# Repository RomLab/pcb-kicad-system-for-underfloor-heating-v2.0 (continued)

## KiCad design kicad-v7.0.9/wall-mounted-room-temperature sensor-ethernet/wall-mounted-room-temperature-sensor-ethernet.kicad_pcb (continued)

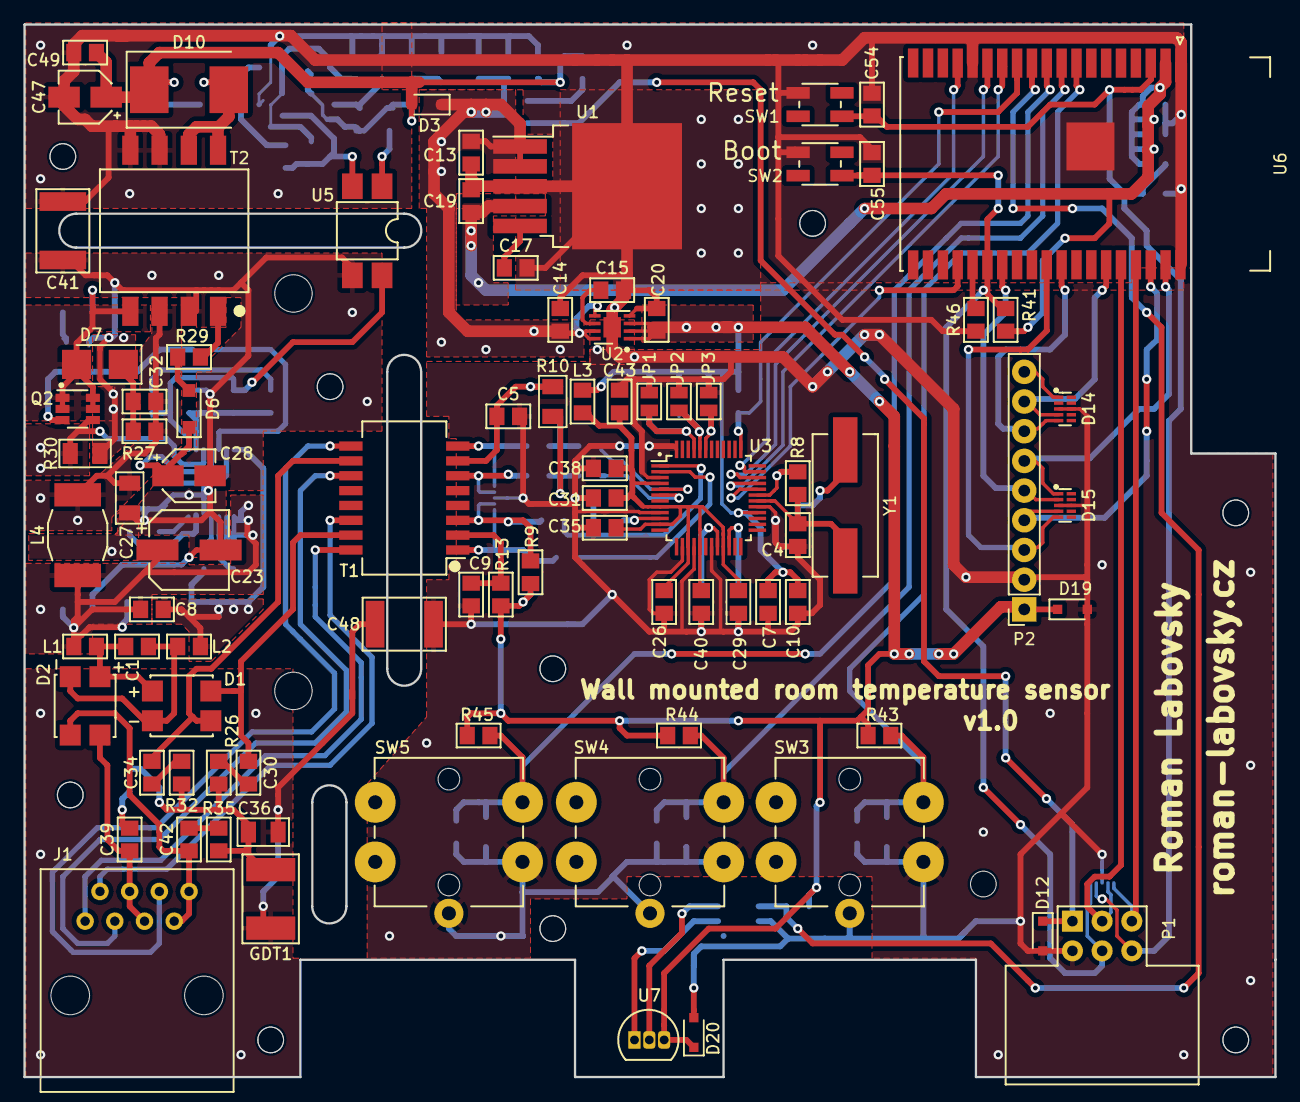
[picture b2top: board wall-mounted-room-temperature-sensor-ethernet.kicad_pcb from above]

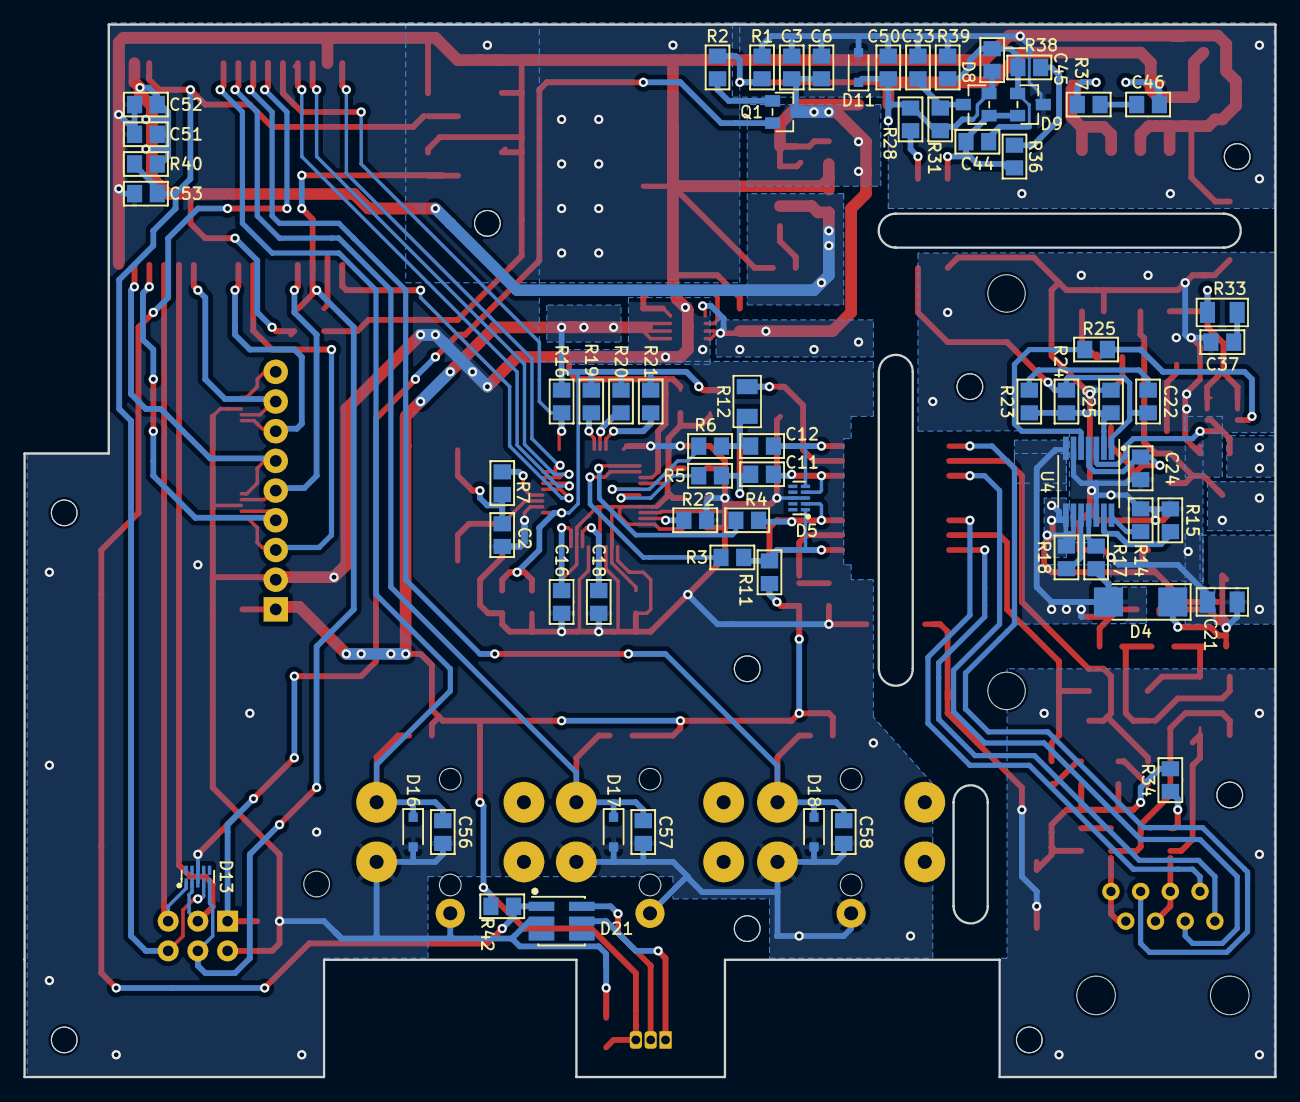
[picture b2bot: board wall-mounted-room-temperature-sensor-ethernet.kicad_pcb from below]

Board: 2 copper layers, 107.0 x 90.0 mm, 165 parts (66 on the bottom side), 97 nets.

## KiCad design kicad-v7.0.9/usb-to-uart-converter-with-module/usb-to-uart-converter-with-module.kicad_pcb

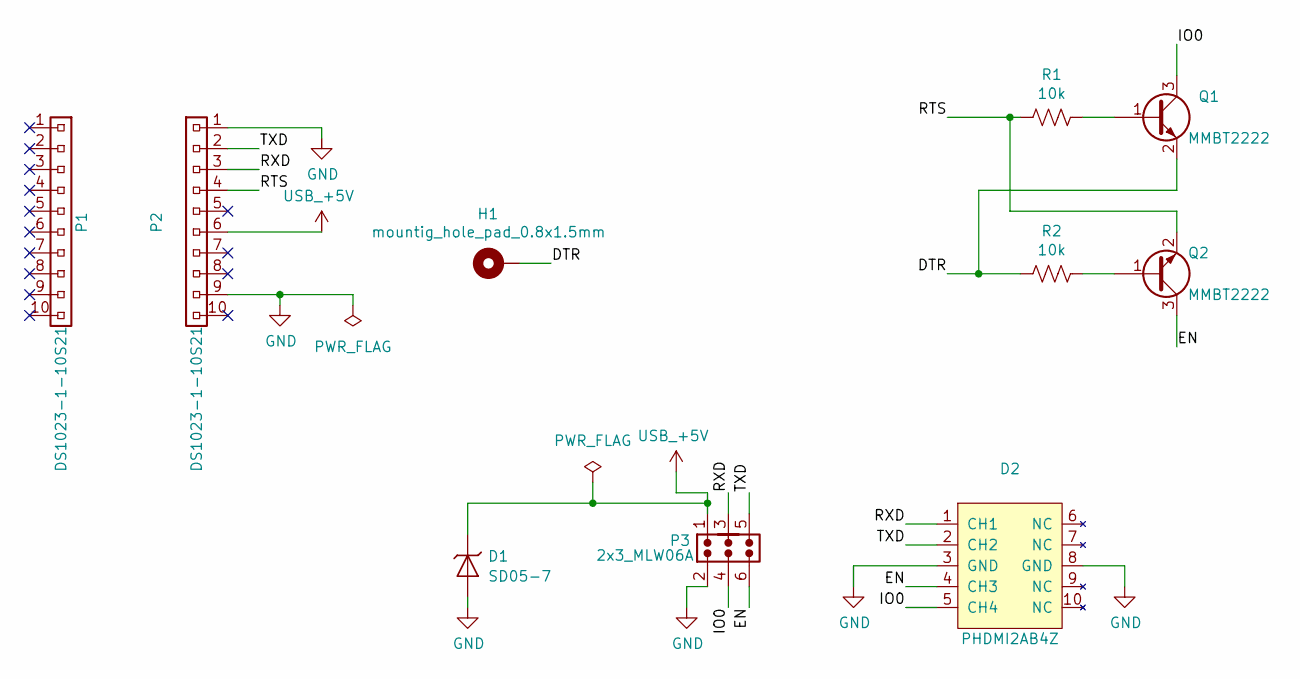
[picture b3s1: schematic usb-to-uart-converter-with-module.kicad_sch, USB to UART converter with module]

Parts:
D1: SD05-7; sod_323
D2: PHDMI2AB4Z; dfn_2510a_10
H1: mountig_hole_pad_0.8x1.5mm
P1, P2: DS1023-1-10S21; 1x10_pin_socket_2.54mm_vertical_8.5mm
P3: 2x3_MLW06A
Q1, Q2: MMBT2222; sot_23_3
R1, R2: 10k; r_0805

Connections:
/DTR: H1.1, Q1.2 (E), R2.1
/EN: D2.4 (CH3), P3.6, Q2.3 (C)
/IO0: D2.5 (CH4), P3.4, Q1.3 (C)
/RTS: P2.4, Q2.2 (E), R1.1
/RXD: D2.1 (CH1), P2.3, P3.3
/TXD: D2.2 (CH2), P2.2, P3.5
GND: D1.2 (A), D2.3 (GND), D2.8 (GND), P2.1, P2.9, P3.2
unnamed: Q1.1 (B), R1.2
unnamed: Q2.1 (B), R2.2
USB_+5V: D1.1 (K), P2.6, P3.1

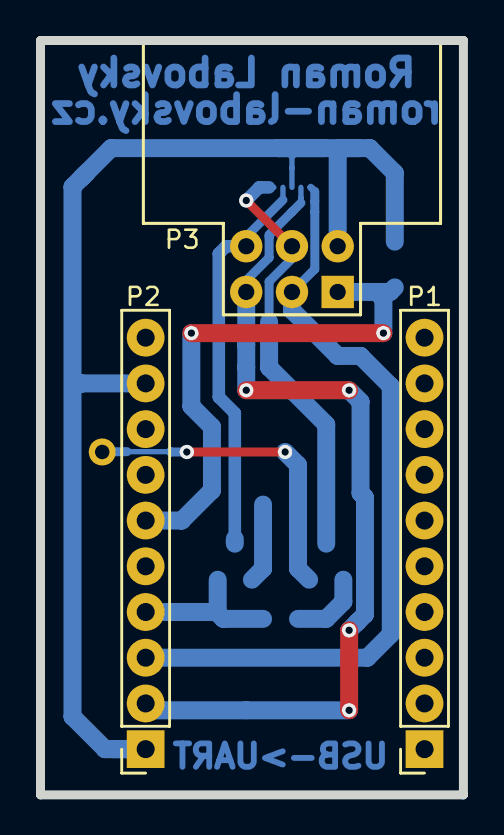
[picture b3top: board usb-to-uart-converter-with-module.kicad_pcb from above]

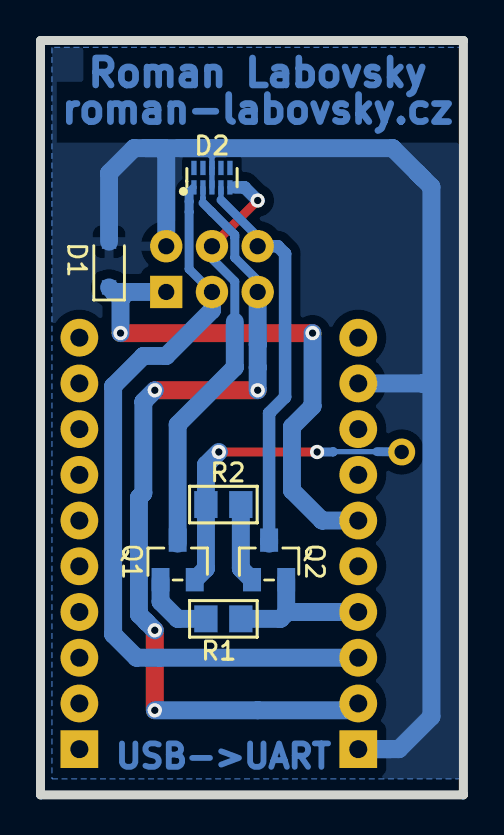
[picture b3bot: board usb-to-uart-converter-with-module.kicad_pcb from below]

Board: 2 copper layers, 23.5 x 41.9 mm, 10 parts (7 on the bottom side), 10 nets.

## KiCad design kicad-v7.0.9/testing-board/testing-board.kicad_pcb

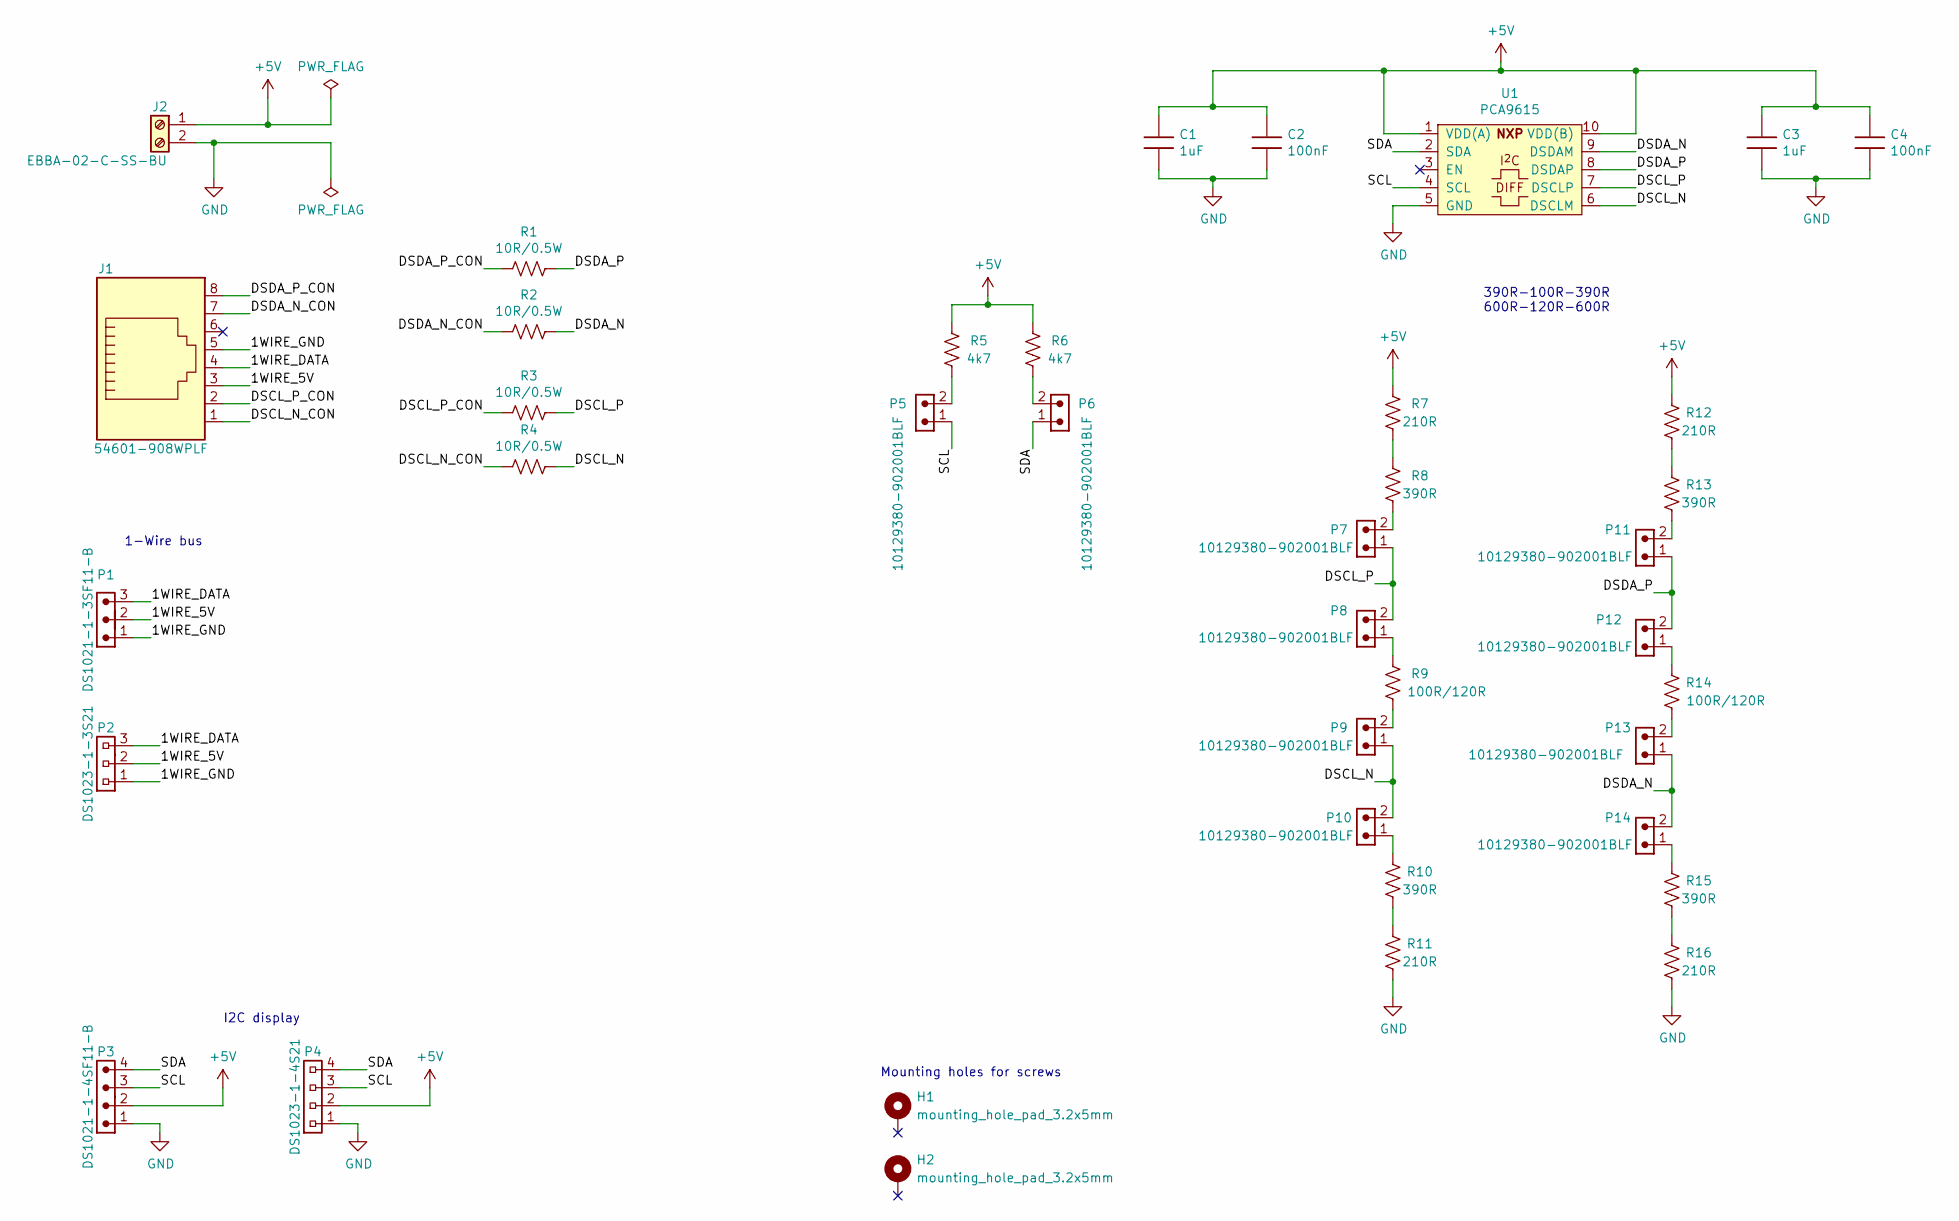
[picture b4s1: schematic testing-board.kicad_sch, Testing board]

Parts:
C1, C3: 1uF; c_1206
C2, C4: 100nF; c_1206
H1, H2: mounting_hole_pad_3.2x5mm
J1: 54601-908WPLF
J2: EBBA-02-C-SS-BU
P1: DS1021-1-3SF11-B; 1x3_pin_header_2.54mm_vertical
P2: DS1023-1-3S21; 1x3_pin_socket_2.54mm_vertical_8.5mm
P3: DS1021-1-4SF11-B; 1x4_pin_header_2.54mm_vertical
P4: DS1023-1-4S21; 1x4_pin_socket_2.54mm_vertical_8.5mm
P5, P6, P7, P8, P9, P10, P11, P12, P13, P14: 10129380-902001BLF; 1x2_pin_header_2.54mm_vertical
R1, R2, R3, R4: 10R/0.5W; r_1206
R5, R6: 4k7; r_1206
R7, R11, R12, R16: 210R; r_1206
R8, R10, R13, R15: 390R; r_1206
R9, R14: 100R/120R; r_1206
U1: PCA9615; tssop_10

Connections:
+5V: C1.1, C2.1, C3.1, C4.1, J2.1, P3.2, P4.2, R5.1, R6.1, R7.1, R12.1, U1.1 (VDD(A)), U1.10 (VDD(B))
/1WIRE_5V: J1.3, P1.2, P2.2
/1WIRE_DATA: J1.4, P1.3, P2.3
/1WIRE_GND: J1.5, P1.1, P2.1
/DSCL_N: P9.1, P10.2, R4.2, U1.6 (DSCLM)
/DSCL_N_CON: J1.1, R4.1
/DSCL_P: P7.1, P8.2, R3.2, U1.7 (DSCLP)
/DSCL_P_CON: J1.2, R3.1
/DSDA_N: P13.1, P14.2, R2.2, U1.9 (DSDAM)
/DSDA_N_CON: J1.7, R2.1
/DSDA_P: P11.1, P12.2, R1.2, U1.8 (DSDAP)
/DSDA_P_CON: J1.8, R1.1
/SCL: P3.3, P4.3, P5.1, U1.4 (SCL)
/SDA: P3.4, P4.4, P6.1, U1.2 (SDA)
GND: C1.2, C2.2, C3.2, C4.2, J2.2, P3.1, P4.1, R11.2, R16.2, U1.5 (GND)
unnamed: P5.2, R5.2
unnamed: P6.2, R6.2
unnamed: P7.2, R8.2
unnamed: P8.1, R9.1
unnamed: P9.2, R9.2
unnamed: P10.1, R10.1
unnamed: P11.2, R13.2
unnamed: P12.1, R14.1
unnamed: P13.2, R14.2
unnamed: P14.1, R15.1
unnamed: R7.2, R8.1
unnamed: R10.2, R11.1
unnamed: R12.2, R13.1
unnamed: R15.2, R16.1

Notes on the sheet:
1-Wire bus
Mounting holes for screws
I2C display
390R-100R-390R 600R-120R-600R

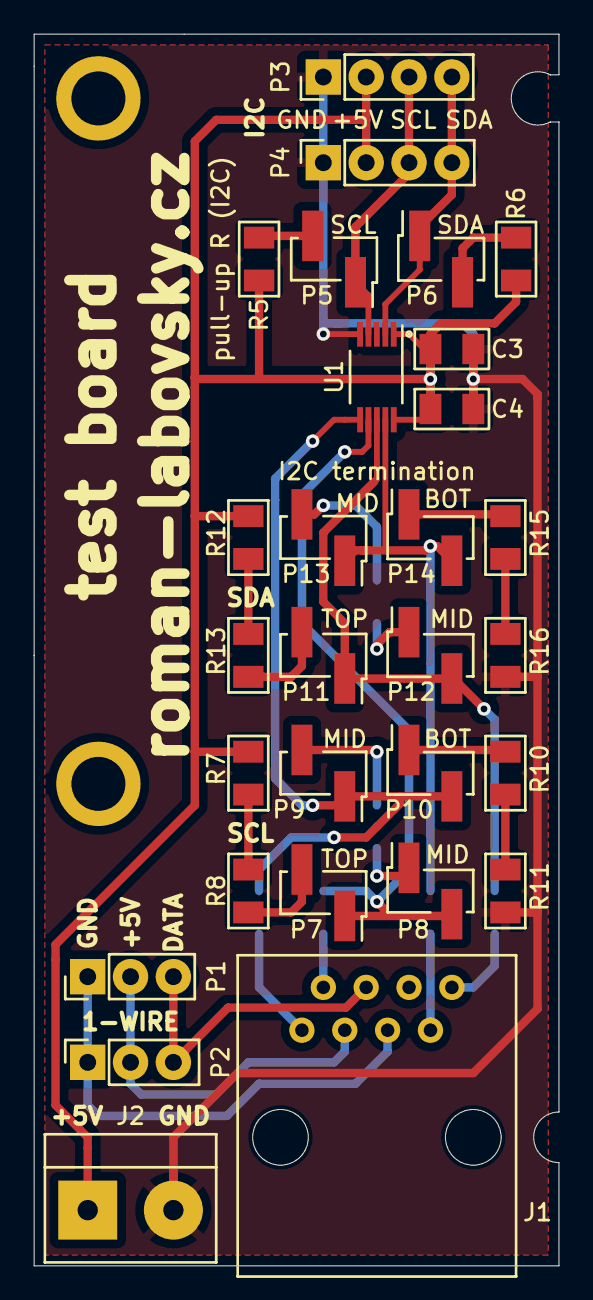
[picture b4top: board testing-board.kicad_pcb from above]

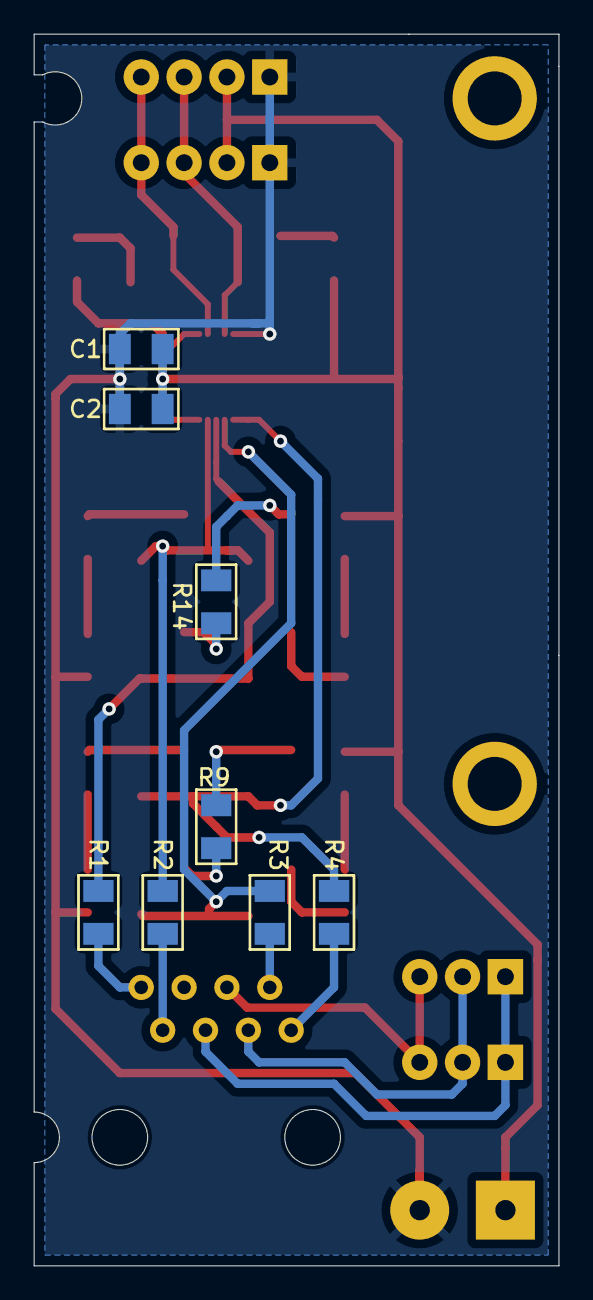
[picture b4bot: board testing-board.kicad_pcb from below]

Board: 2 copper layers, 31.1 x 73.0 mm, 39 parts (8 on the bottom side), 29 nets.

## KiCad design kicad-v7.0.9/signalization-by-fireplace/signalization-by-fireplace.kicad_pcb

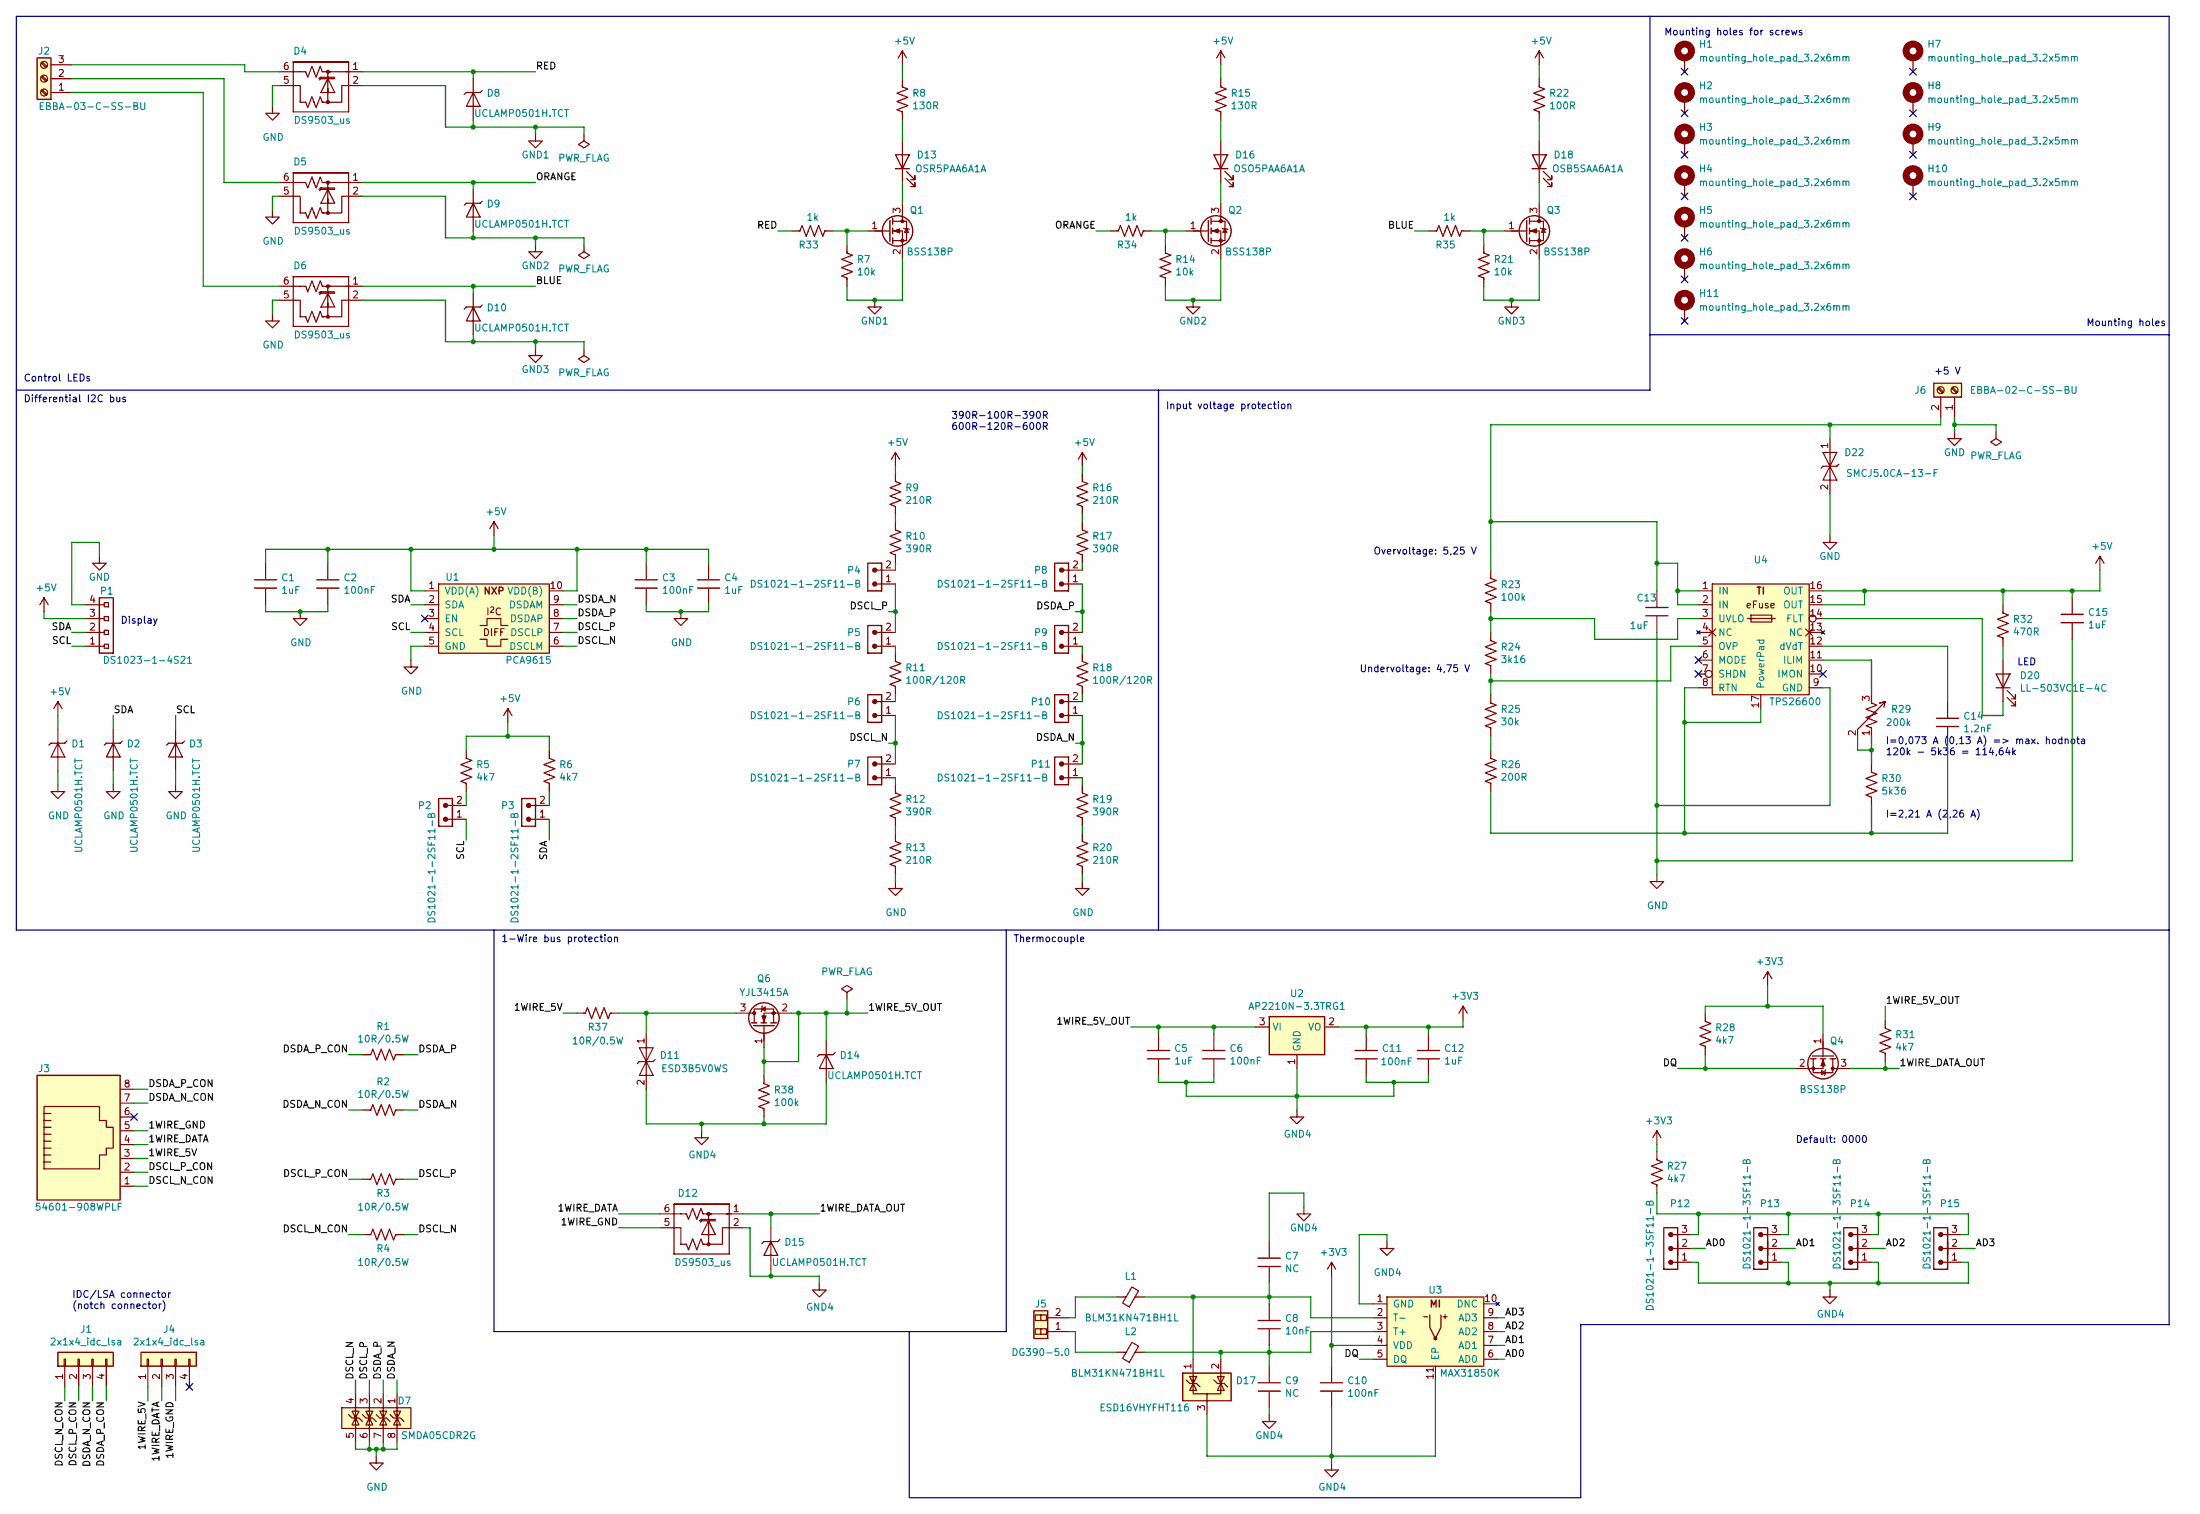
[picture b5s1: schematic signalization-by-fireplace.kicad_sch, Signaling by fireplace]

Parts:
C1, C4, C5, C12, C13, C15: 1uF; c_1206
C2, C3, C6, C10, C11: 100nF; c_1206
C7, C9: NC; c_1206
C8: 10nF; c_1206
C14: 1.2nF; c_1206
D1, D2, D3, D8, D9, D10, D14, D15: UCLAMP0501H.TCT; sod_523
D4, D5, D6, D12: DS9503_us; tsoc_6
D7: SMDA05CDR2G; soic_8_3.9mmx4.9mm
D11: ESD3B5V0WS; sod_323
D13: OSR5PAA6A1A; led_d10mm_2.54mm
D16: OSO5PAA6A1A; led_d10mm_2.54mm
D17: ESD16VHYFHT116; sot_23
D18: OSB5SAA6A1A; led_d10mm_2.54mm
D20: LL-503VC1E-4C; led_d5mm_2.54mm
D22: SMCJ5.0CA-13-F; smc
H1, H2, H3, H4, H5, H6, H11: mounting_hole_pad_3.2x6mm
H7, H8, H9, H10: mounting_hole_pad_3.2x5mm
J1, J4: 2x1x4_idc_lsa; 1x4_idc_lsa_connector_general
J2: EBBA-03-C-SS-BU
J3: 54601-908WPLF
J5: DG390-5.0; DG390-5.0-02P-12-00A(H)
J6: EBBA-02-C-SS-BU
L1, L2: BLM31KN471BH1L; ferrite_bead_1206
P1: DS1023-1-4S21; 1x4_pin_socket_2.54mm_vertical_8.5mm
P2, P3, P4, P5, P6, P7, P8, P9, P10, P11: DS1021-1-2SF11-B; 1x2_pin_header_2.54mm_vertical
P12, P13, P14, P15: DS1021-1-3SF11-B; 1x3_pin_header_2.54mm_vertical
Q1, Q2, Q3, Q4: BSS138P; sot_323
Q6: YJL3415A; sot_23
R1, R2, R3, R4, R37: 10R/0.5W; r_1206
R5, R6, R27, R28, R31: 4k7; r_1206
R7, R14, R21: 10k; r_1206
R8, R15: 130R; r_1206
R9, R13, R16, R20: 210R; r_1206
R10, R12, R17, R19: 390R; r_1206
R11, R18: 100R/120R; r_1206
R22: 100R; r_1206
R23, R38: 100k; r_1206
R24: 3k16; r_1206
R25: 30k; r_1206
R26: 200R; r_1206
R29: 200k; T93YB
R30: 5k36; r_1206
R32: 470R; r_1206
R33, R34, R35: 1k; r_1206
U1: PCA9615; tssop_10
U2: AP2210N-3.3TRG1; sot_23_3
U3: MAX31850K; tdfn_10_ep
U4: TPS26600; htssop_16_6.6mm×5.1mm

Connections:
+3V3: C10.1, C11.1, C12.1, Q4.1 (G), R27.1, R28.1, U2.2 (VO), U3.4 (VDD)
+5V: C1.1, C2.1, C3.1, C4.1, C15.1, D1.1 (K), P1.3, R5.1, R6.1, R8.1, R9.1, R15.1, R16.1, R22.1, R32.1, U1.1 (VDD(A)), U1.10 (VDD(B)), U4.15 (OUT), U4.16 (OUT)
/1WIRE_5V: J3.3, J4.1, R37.1
/1WIRE_5V_OUT: C5.1, C6.1, D14.1 (K), Q6.1 (G), Q6.2 (S), R31.1, R38.1, U2.3 (VI)
/1WIRE_DATA: D12.6 (K), J3.4, J4.2
/1WIRE_DATA_OUT: D12.1 (K), D15.1 (K), Q4.3 (D), R31.2
/1WIRE_GND: D12.5 (A), J3.5, J4.3
/AD0: P12.2, U3.6 (AD0)
/AD1: P13.2, U3.7 (AD1)
/AD2: P14.2, U3.8 (AD2)
/AD3: P15.2, U3.9 (AD3)
/BLUE: D6.1 (K), D10.1 (K), R35.2
/DQ: Q4.2 (S), R28.2, U3.5 (DQ)
/DSCL_N: D7.4 (A), P6.1, P7.2, R4.2, U1.6 (DSCLM)
/DSCL_N_CON: J1.1, J3.1, R4.1
/DSCL_P: D7.3 (A), P4.1, P5.2, R3.2, U1.7 (DSCLP)
/DSCL_P_CON: J1.2, J3.2, R3.1
/DSDA_N: D7.1 (A), P10.1, P11.2, R2.2, U1.9 (DSDAM)
/DSDA_N_CON: J1.3, J3.7, R2.1
/DSDA_P: D7.2 (A), P8.1, P9.2, R1.2, U1.8 (DSDAP)
/DSDA_P_CON: J1.4, J3.8, R1.1
/ORANGE: D5.1 (K), D9.1 (K), R34.2
/RED: D4.1 (K), D8.1 (K), R33.2
/SCL: D3.1 (K), P1.1, P2.1, U1.4 (SCL)
/SDA: D2.1 (K), P1.2, P3.1, U1.2 (SDA)
GND: C1.2, C2.2, C3.2, C4.2, C13.2, C15.2, D1.2 (A), D2.2 (A), D3.2 (A), D4.5 (A), D5.5 (A), D6.5 (A), D7.5 (A), D7.6 (A), D7.7 (A), D7.8 (A), D22.2 (A2), J6.1, P1.4, R13.2, R20.2, U1.5 (GND), U4.9 (GND)
GND1: D4.2 (A), D8.2 (A), Q1.2 (S), R7.2
GND2: D5.2 (A), D9.2 (A), Q2.2 (S), R14.2
GND3: D6.2 (A), D10.2 (A), Q3.2 (S), R21.2
GND4: C5.2, C6.2, C7.1, C9.2, C10.2, C11.2, C12.2, D11.2 (A2), D12.2 (A), D14.2 (A), D15.2 (A), D17.3 (A), P12.1, P13.1, P14.1, P15.1, R38.2, U2.1 (GND), U3.1 (GND), U3.11 (EP)
unnamed: D11.1 (A1), Q6.3 (D), R37.2
unnamed: D13.2 (A), R8.2
unnamed: D13.1 (K), Q1.3 (D)
unnamed: D16.2 (A), R15.2
unnamed: D16.1 (K), Q2.3 (D)
unnamed: D18.2 (A), R22.2
unnamed: D18.1 (K), Q3.3 (D)
unnamed: D20.2 (A), R32.2
unnamed: D20.1 (K), U4.14 (FLT)
unnamed: C13.1, D22.1 (A1), J6.2, R23.1, U4.1 (IN), U4.2 (IN)
unnamed: D6.6 (K), J2.1
unnamed: D5.6 (K), J2.2
unnamed: D4.6 (K), J2.3
unnamed: J5.1, L2.1
unnamed: J5.2, L1.1
unnamed: P2.2, R5.2
unnamed: P3.2, R6.2
unnamed: P4.2, R10.2
unnamed: P5.1, R11.1
unnamed: P6.2, R11.2
unnamed: P7.1, R12.1
unnamed: P8.2, R17.2
unnamed: P9.1, R18.1
unnamed: P10.2, R18.2
unnamed: P11.1, R19.1
unnamed: P12.3, P13.3, P14.3, P15.3, R27.2
unnamed: Q1.1 (G), R7.1, R33.1
unnamed: Q2.1 (G), R14.1, R34.1
unnamed: Q3.1 (G), R21.1, R35.1
unnamed: R9.2, R10.1
unnamed: R12.2, R13.1
unnamed: R16.2, R17.1
unnamed: R19.2, R20.1
unnamed: R25.2, R26.1
unnamed: R29.1, R29.2, R30.2
unnamed: C8.2, C9.1, D17.2 (K), L2.2, U3.3 (T+)
unnamed: C7.2, C8.1, D17.1 (K), L1.2, U3.2 (T-)
unnamed: R29.3, U4.11 (ILIM)
unnamed: R24.2, R25.1, U4.5 (OVP)
unnamed: C14.2, R26.2, R30.1, U4.8 (RTN), U4.17 (PowerPad)
unnamed: R23.2, R24.1, U4.3 (UVLO)
unnamed: C14.1, U4.12 (dVdT)

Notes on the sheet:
Default: 0000
Mounting holes for screws
Display
Overvoltage: 5,25 V
390R-100R-390R 600R-120R-600R
LED
Thermocouple
1-Wire bus protection
+5 V
IDC/LSA connector (notch connector)
Undervoltage: 4,75 V
Differential I2C bus
Input voltage protection
I=2,21 A (2,26 A)
I=0,073 A (0,13 A) => max. hodnota 120k - 5k36 = 114,64k
Control LEDs
Mounting holes

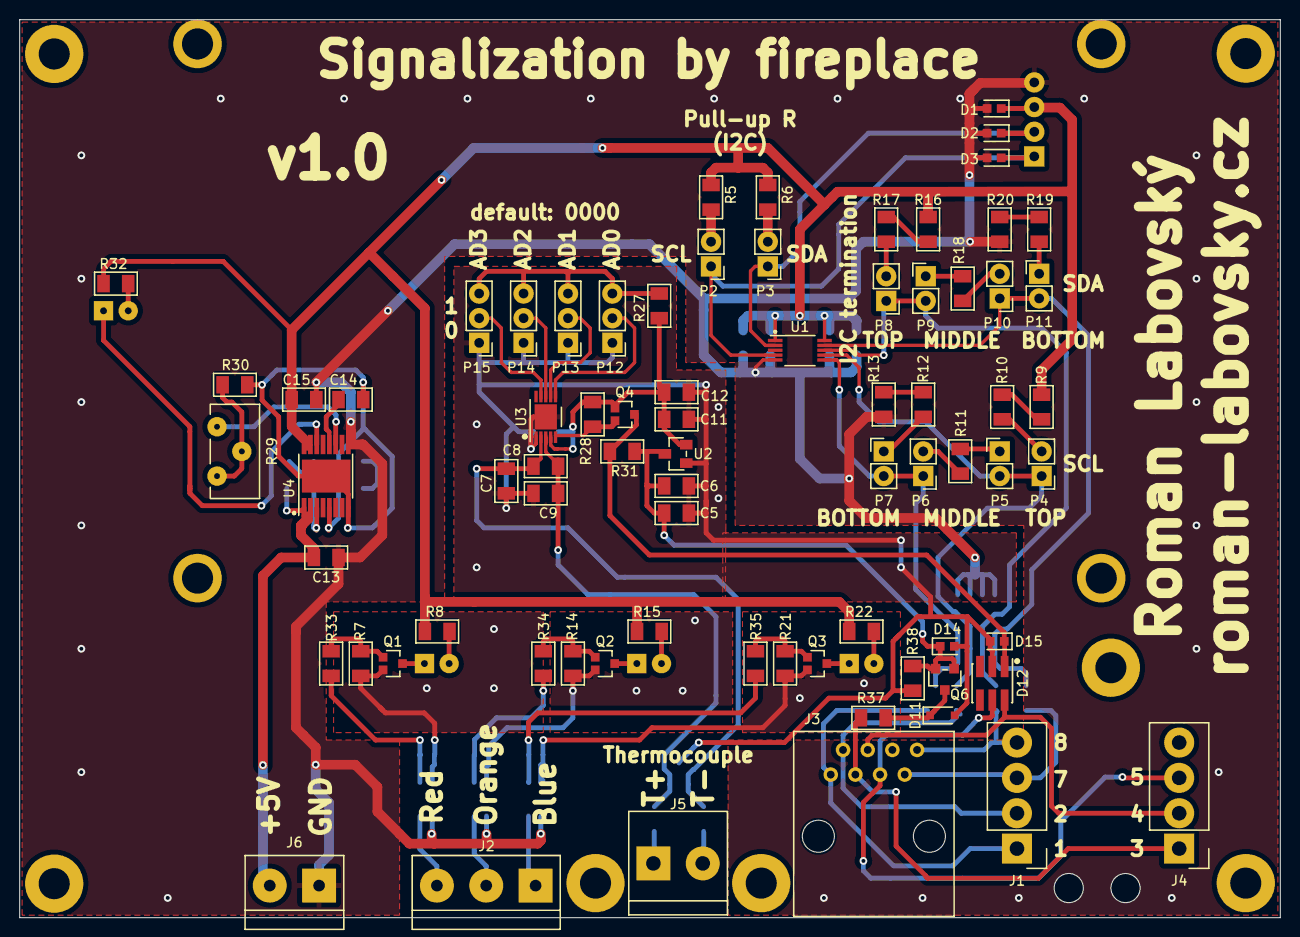
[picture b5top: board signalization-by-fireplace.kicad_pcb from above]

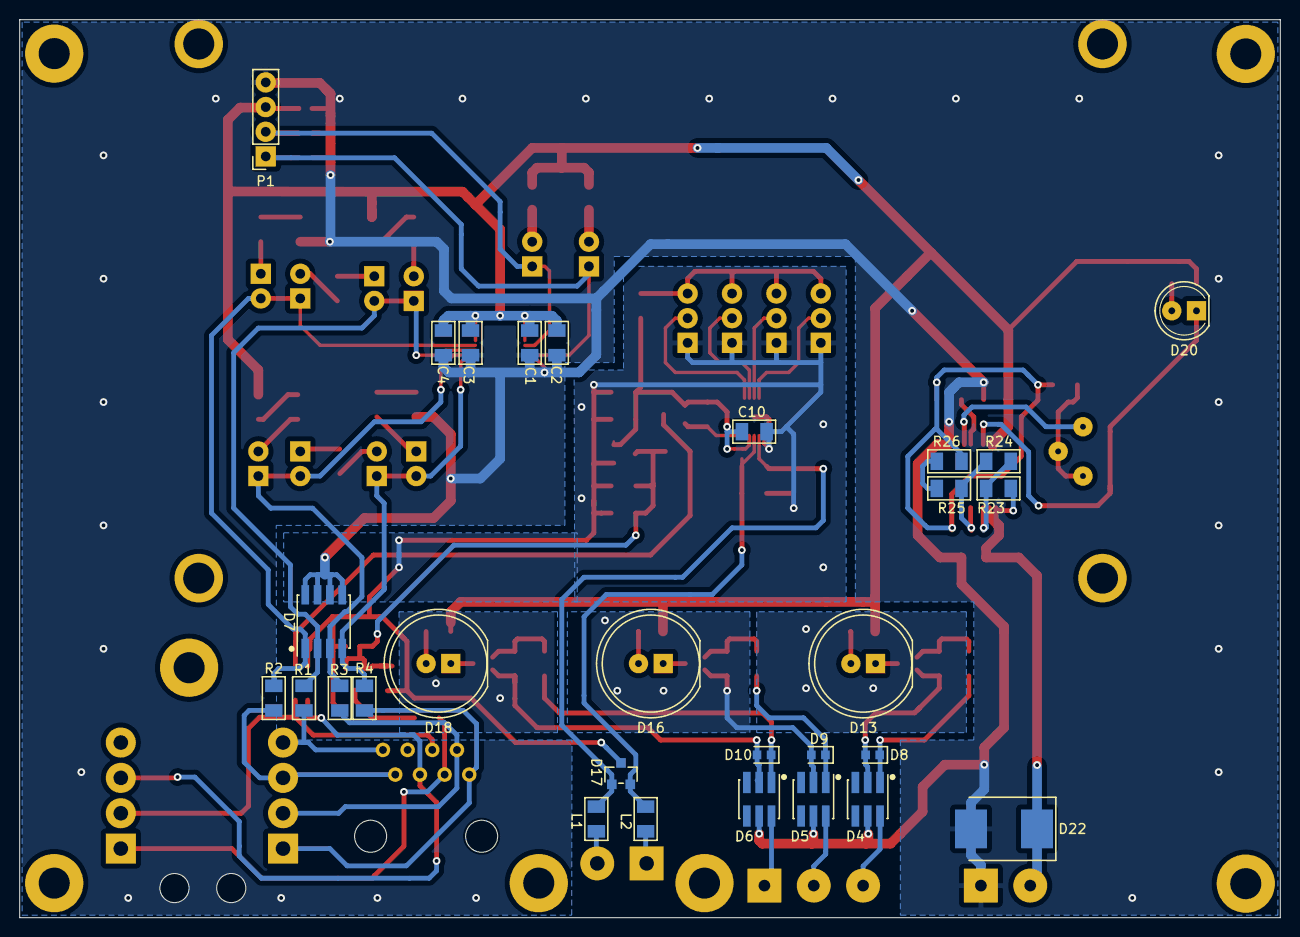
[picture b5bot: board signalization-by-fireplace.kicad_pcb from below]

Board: 2 copper layers, 129.8 x 92.5 mm, 115 parts (29 on the bottom side), 72 nets.
